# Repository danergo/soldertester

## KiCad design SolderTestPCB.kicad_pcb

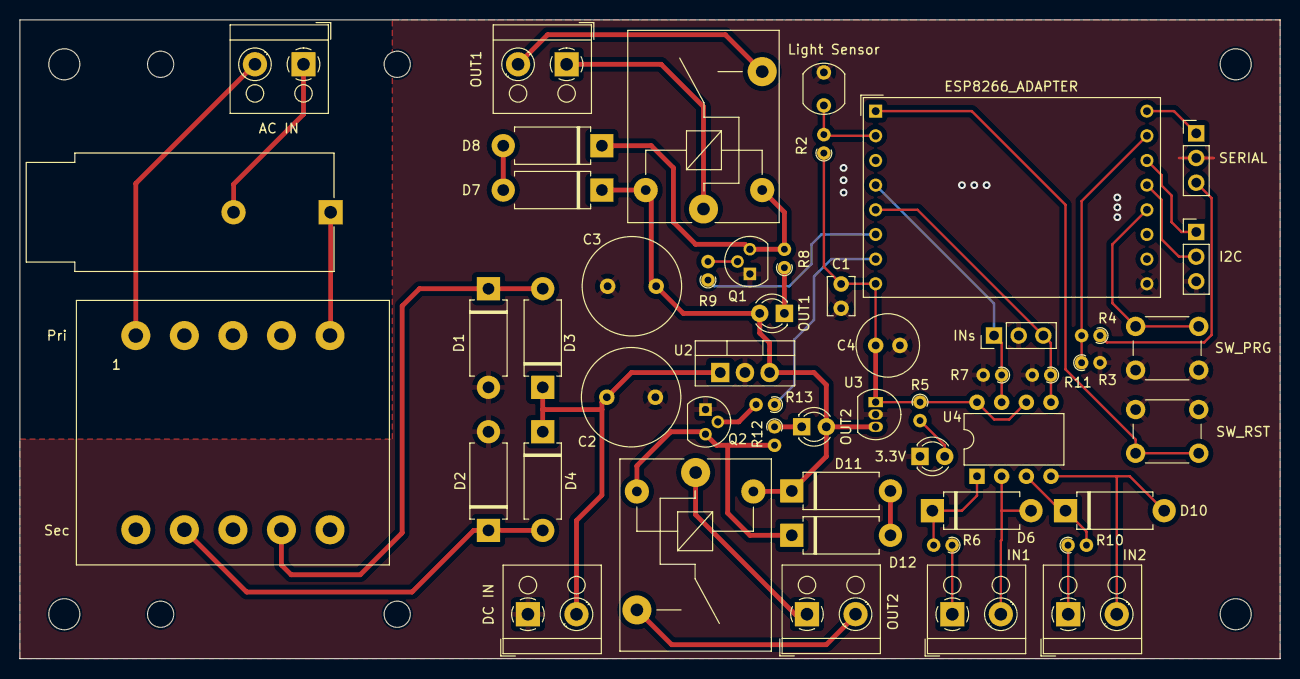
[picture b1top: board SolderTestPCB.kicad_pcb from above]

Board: 2 copper layers, 129.8 x 65.8 mm, 59 parts (0 on the bottom side), 40 nets.

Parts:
3.3V: LED; LED_D3.0mm
AC IN: Screw_Terminal_01x02; TerminalBlock_RND_205-00001_1x02_P5.00mm_Horizontal
C1: 100nF; C_Disc_D3.8mm_W2.6mm_P2.50mm
C2, C3: C; C_Radial_D10.0mm_H12.5mm_P5.00mm
C4: C; C_Radial_D6.3mm_H7.0mm_P2.50mm
D1, D2, D3, D4: D_45deg; D_DO-15_P10.16mm_Horizontal
D6, D7, D10, D11: D; D_DO-15_P10.16mm_Horizontal
D8, D12: D_Zener; D_DO-15_P10.16mm_Horizontal
DC IN: Screw_Terminal_01x02; TerminalBlock_RND_205-00001_1x02_P5.00mm_Horizontal
ESP8266_ADAPTER: ESP-12; HOPERF_RFM9XW_THT
F1: Fuse; Fuseholder_Cylinder-5x20mm_Schurter_FAB_0031-355x_Horizonta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
H1, H2, H3, H4: MountingHole; MountingHole_3.2mm_M3
H5, H6, H7, H8: MountingHole; MountingHole_2.7mm_M2.5
I2C: CON_I2C; PinHeader_1x03_P2.54mm_Vertical
IN1, IN2: Screw_Terminal_01x02; TerminalBlock_RND_205-00001_1x02_P5.00mm_Horizontal
INs: CON_INPUT; PinHeader_1x03_P2.54mm_Vertical
K1, K2: Relay_SPST-NO; Relay_SPST_SANYOU_SRD_Series_Form_A
Light Sensor: R_Photo; R_LDR_5.1x4.3mm_P3.4mm_Vertical
OUT1, OUT2#2: LED; LED_D3.0mm
OUT1#2, OUT2: Screw_Terminal_01x02; TerminalBlock_RND_205-00001_1x02_P5.00mm_Horizontal
Q1, Q2: Q_NPN_EBC; TO-92
R2, R3, R4, R5, R6, R7, R8, R9, R10, R11, R12, R13: R; R_Axial_DIN0204_L3.6mm_D1.6mm_P1.90mm_Vertical
SERIAL: CON_SERIAL; PinHeader_1x03_P2.54mm_Vertical
SW_PRG: SW_PRG; SW_PUSH_6mm_H4.3mm
SW_RST: SW_RST; SW_PUSH_6mm_H4.3mm
TR1: TRANSF1; Transformer_CHK_EI30-2VA_1xSec
U2: L7805; TO-220-3_Vertical
U3: L78L33_TO92; TO-92_Inline
U4: LTV-827; DIP-8_W7.62mm

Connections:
+5V: C3.1, D7.1 (K), D11.1 (K), K1.A1, K2.A1, OUT1.2 (A), OUT2#2.2 (A), U2.3 (OUT), U3.3 (VI)
/Output0/Control: ESP8266_ADAPTER.6 (GPIO12), R9.1
/Output1/Control: ESP8266_ADAPTER.7 (GPIO13), R13.1
GND: 3.3V.1 (K), C1.2, C2.2, C3.2, C4.2, D1.2 (A), D2.2 (A), DC IN.1, ESP8266_ADAPTER.9 (GND), I2C.3, INs.2, Light Sensor.1, Q1.1 (E), Q2.1 (E), R3.2, R7.2, R11.2, SERIAL.2, SW_PRG.2, SW_RST.1, U2.2 (GND), U3.2 (GND)
unnamed: D1.1 (K), D3.2 (A), TR1.7
unnamed: D2.1 (K), D4.2 (A), TR1.9
unnamed: C2.1, D3.1 (K), D4.1 (K), DC IN.2, U2.1 (IN)
unnamed: 3.3V.2 (A), R5.2
unnamed: D6.2 (A), IN1.2, U4.2
unnamed: D6.1 (K), R6.2, U4.1
unnamed: D7.2 (A), D8.2 (A)
unnamed: D8.1 (K), K1.A2, Q1.3 (C), R8.2
unnamed: OUT1.1 (K), R8.1
unnamed: D10.2 (A), IN2.2, U4.4
unnamed: D10.1 (K), R10.2, U4.3
unnamed: D11.2 (A), D12.2 (A)
unnamed: D12.1 (K), K2.A2, Q2.3 (C), R12.2
unnamed: OUT2#2.1 (K), R12.1
unnamed: F1.1, TR1.5
unnamed: ESP8266_ADAPTER.4 (GPIO16), INs.1, R7.1, U4.7
unnamed: ESP8266_ADAPTER.5 (GPIO14), INs.3, R11.1, U4.5
unnamed: ESP8266_ADAPTER.14 (GPIO5), I2C.1
unnamed: ESP8266_ADAPTER.13 (GPIO4), I2C.2
unnamed: ESP8266_ADAPTER.16 (TXD), SERIAL.1
unnamed: R4.1, SERIAL.3
unnamed: AC IN.1, F1.2
unnamed: AC IN.2, TR1.1
unnamed: IN1.1, R6.1
unnamed: K1.13, OUT1#2.1
unnamed: K1.14, OUT1#2.2
unnamed: IN2.1, R10.1
unnamed: K2.13, OUT2.1
unnamed: K2.14, OUT2.2
unnamed: Q1.2 (B), R9.2
unnamed: Q2.2 (B), R13.2
unnamed: ESP8266_ADAPTER.2 (ADC), Light Sensor.2, R2.2
unnamed: ESP8266_ADAPTER.12 (GPIO0), SW_PRG.1
unnamed: ESP8266_ADAPTER.1 (REST), SW_RST.2
unnamed: ESP8266_ADAPTER.15 (RXD), R3.1, R4.2
VCC: C1.1, C4.1, ESP8266_ADAPTER.8 (VCC), R2.1, R5.1, U3.1 (VO), U4.6, U4.8

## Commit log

2024-03-16 Initial schematic
2024-04-09 Schematic ready; PCB needs silkscreen
2024-04-13 PCB Layout finished (RTM)
